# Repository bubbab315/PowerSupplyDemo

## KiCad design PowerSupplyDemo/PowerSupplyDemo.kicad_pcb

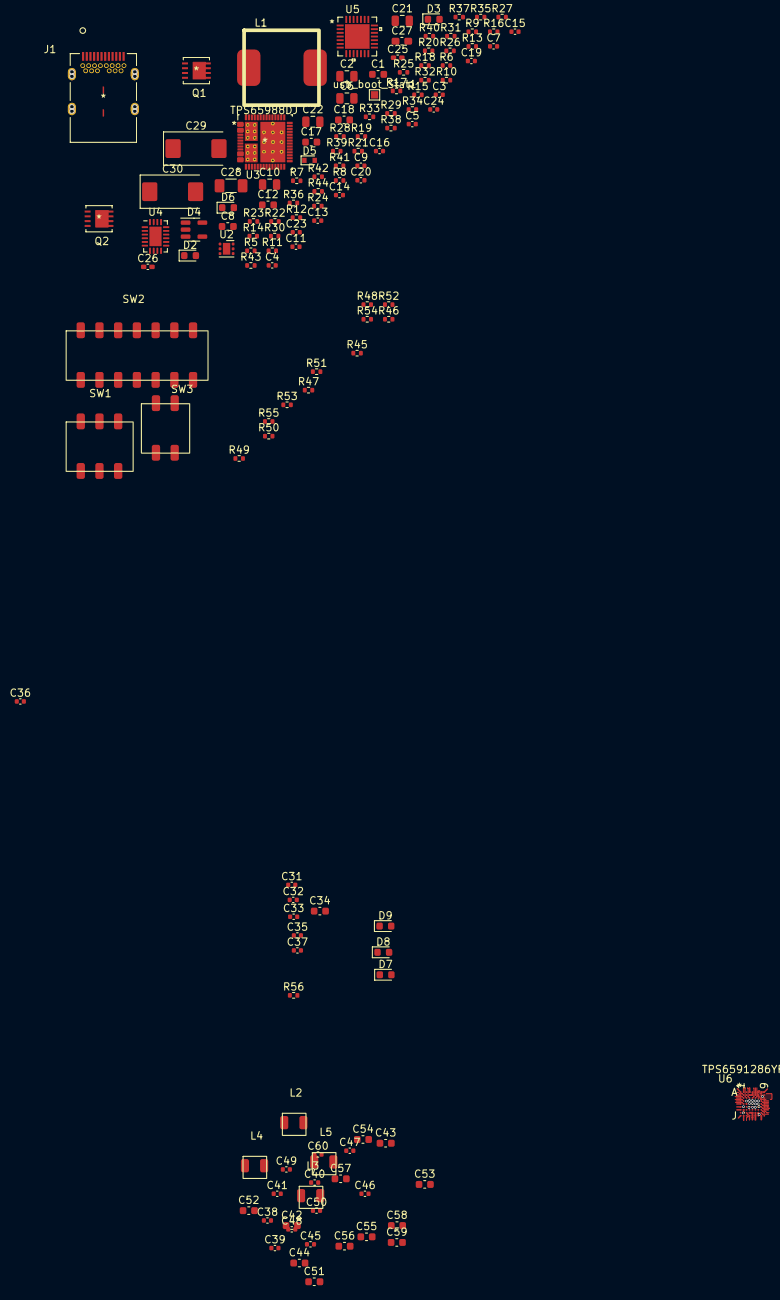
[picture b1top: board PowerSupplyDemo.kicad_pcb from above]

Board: 8 copper layers, 137 parts (0 on the bottom side), 88 nets.

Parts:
C1, C18: 4.7uF; C_0603_1608Metric
C2, C6, C21: 10uF; C_0805_2012Metric
C3: 1000p; C_0402_1005Metric
C4: 200p; C_0402_1005Metric
C5: 470p; C_0402_1005Metric
C7, C16, C24: 1uF; C_0402_1005Metric
C8, C12, C17: 4.7uF 10V; C_0603_1608Metric
C9, C13, C14, C15, C19: 0.1uF; C_0402_1005Metric
C10: 47uF 25V(dnp); C_0805_2012Metric
C11: 0.01uF; C_0402_1005Metric
C20: 77.5n; C_0402_1005Metric
C22: 47uF; C_0805_2012Metric
C23: tbd(opt); C_0402_1005Metric
C25: 2.2uF; C_0402_1005Metric_Pad0.74x0.62mm_HandSolder
C26: 4.7uF; C_0402_1005Metric_Pad0.74x0.62mm_HandSolder
C27: 10uF; C_0603_1608Metric_Pad1.08x0.95mm_HandSolder
C28: 47uF; C_1206_3216Metric_Pad1.33x1.80mm_HandSolder
C29, C30: 100u; CP_EIA-7343-15_Kemet-W
C31, C33, C39, C48, C49, C60: 4.7uF; C_0402_1005Metric
C32, C35, C37: 100nF; C_0402_1005Metric
C34, C42, C43, C44, C51, C52, C53, C54, C55, C56, C57, C58, C59: 10uF; C_0603_1608Metric
C36, C38, C40, C41, C45, C46, C47, C50: 2.2uF; C_0402_1005Metric
D2, D3: D_TVS(dnp); D_0603_1608Metric
D4: SP0504BAHT; SOT-23-5
D5: BAT54XV2T1; D_SOD-523
D6, D9: red; LED_0603_1608Metric
D7: green; LED_0603_1608Metric
D8: yellow; LED_0603_1608Metric
J1: USB_C; USB_C_632723300011
L1: IHLP4040DZER1R0M5A
L2, L3, L4, L5: 1uH; SPM3012T-1R0M
Q1, Q2: BSZ060NE2LSATMA1
R5, R6, R7, R8, R15, R16, R17, R18, R20, R21: 10k; R_0402_1005Metric
R9, R14, R22, R23, R36, R37, R38: 0; R_0402_1005Metric
R10, R24, R27: dnp; R_0402_1005Metric
R11: 101.675k; R_0402_1005Metric
R12: 100k; R_0402_1005Metric
R13: 12k; R_0402_1005Metric
R19: 5; R_0402_1005Metric
R25: 2.2ohm; R_0402_1005Metric
R26: 3k 1%; R_0402_1005Metric
R28, R29, R32, R33: 1k 1%; R_0402_1005Metric
R30: 90.9k; R_0402_1005Metric
R31: 20.0k; R_0402_1005Metric
R34: 150 1%; R_0402_1005Metric
R35: 150; R_0402_1005Metric
R39, R40, R41, R42, R43, R44: 0(DNP); R_0402_1005Metric
R45, R46, R47, R48, R49, R50, R51, R52, R53, R54, R55: 4.7K; R_0402_1005Metric
R56: 0(dnp); R_0402_1005Metric
SW1: 219-3LPSTR
SW2: 219-7LPSTR
SW3: 219-2LPST
U2: TVS2200DRV; WSON-6-1EP_2x2mm_P0.65mm_EP1x1.6mm
U3: TPS65988DJ; TPS65988DHRSHR
U4: LTC3833IUDC; QFN-20-1EP_3x4mm_P0.5mm_EP1.65x2.65mm
U5: CP2102N-A01-GQFN28
U6: TPS6591286YFFR
usb_boot_Stat1: usb_boot_Stat; TestPoint_Pad_1.0x1.0mm

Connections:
/PMIC/EN1: R45.2, SW2.1, U6.E8 (EN1/DCDC1__SEL)
/PMIC/EN2: R47.2, SW2.2, U6.D8 (EN2/DCDC2__SEL)
/PMIC/EN3: R49.2, SW2.3, U6.C6 (EN3/DCDC3__SEL)
/PMIC/EN4: R51.2, SW2.4, U6.C5 (EN4/DCDC4__SEL)
/PMIC/EN_LS0: R54.2, SW2.6, U6.C3 (EN_LS0)
/PMIC/EN_LS1: R53.2, SW2.5, U6.C2 (EN_LS1)
/PMIC/LDOA: C38.1, SW1.4, SW1.5, SW1.6, SW2.8, SW2.9, SW2.10, SW2.11, SW2.12, SW2.13, SW2.14, U6.D3 (NPWRON), U6.G3 (LDOAO)
/PMIC/POS_1P8_IO: C33.1, C35.1, U6.F7 (VDDIO), U6.J1 (VLDO10)
/PMIC/Sleep: R55.2, SW2.7, U6.G4 (SLEEP/PWR__REQ)
/PMIC/config1: R50.2, SW1.3, U6.E2 (CONFIG1)
/PMIC/config2: R48.2, SW1.2, U6.D2 (CONFIG2)
/PMIC/iic_or_spi_cntrl: R46.2, SW1.1, U6.E7 (DEF_SPI__I2C-GPIO)
/input_power/ADCIN1: R33.1, R34.2, U3.6 (ADCIN1)
/input_power/CP2102VDD: C17.1, C19.1, R32.1, U5.6 (VDD)
/input_power/DRAIN1: U3.8 (DRAIN1), U3.15 (DRAIN1), U3.19 (DRAIN1), U3.58 (DRAIN1)
/input_power/DRAIN2: U3.7 (DRAIN2), U3.52 (DRAIN2), U3.56 (DRAIN2), U3.57 (DRAIN2)
/input_power/HRESET: R14.1, U3.44 (HRESET)
/input_power/I2C1_IRQ: R20.1, R38.2, U3.29 (~I2C1_IRQ)
/input_power/I2C1_SCL: R15.1, R36.2, U3.27 (I2C1_SCL)
/input_power/I2C1_SDA: R17.1, R37.2, U3.28 (I2C1_SDA)
/input_power/I2C2_IRQ: R21.1, R41.2, U3.34 (~I2C2_IRQ)
/input_power/I2C2_SCL: R16.1, R39.2, U3.32 (I2C2_SCL)
/input_power/I2C2_SDA: R18.1, R40.2, U3.33 (I2C2_SDA)
/input_power/I2C3_IRQ: R5.1, R44.2, U3.23 (~I2C3_IRQ(GPIO7))
/input_power/I2C3_SCL: R7.1, R42.2, U3.21 (I2C3_SCL(GPIO5))
/input_power/I2C3_SDA: R6.1, R43.2, U3.22 (I2C3_SDA(GPIO6))
/input_power/LDO_1P8: C1.1, U3.35 (LDO_1V8)
/input_power/LDO_3P3: C2.1, R5.2, R6.2, R7.2, R15.2, R16.2, R17.2, R18.2, R20.2, R21.2, R33.2, U3.9 (LDO_3V3)
/input_power/PDVIN_3P3: C6.1, U3.5 (VIN_3V3)
/input_power/Sense+: C20.2, R26.1, R27.2, U4.18 (SENSE+)
/input_power/VCONN1_CC1: D3.2 (A2), J1.A5 (CC), U3.24 (C1_CC1)
/input_power/VCONN1_CC2: D2.2 (A2), J1.B5 (VCONN), U3.26 (C1_CC2)
/input_power/V_RNG: R9.1, R10.2, R12.2, U4.5 (V_RNG)
/input_power/boost: C14.1, R19.1, U4.16 (BOOST)
/input_power/current_sense+: C14.2, L1.1, Q1.1, Q1.2, Q1.3, Q2.5, Q2.6, Q2.7, Q2.8, R26.2, U4.14 (SW)
/input_power/int_vcc: C12.1, D5.2 (A), R9.2, U4.9 (MODE/PLL_IN), U4.11 (INT_VCC)
GND: C1.2, C2.2, C3.2, C4.1, C5.2, C6.2, C7.2, C8.2, C9.2, C10.2, C11.2, C12.2, C13.2, C15.2, C16.2, C17.2, C18.2, C19.2, C21.2, C22.2, C24.2, C25.2, C26.2, C27.2, C28.2, C29.2, C30.2, C31.2, C32.2, C33.2, C34.2, C35.2, C36.2, C37.2, C38.2, C39.2, C40.2, C41.2, C42.2, C43.2, C44.2, C45.2, C46.2, C47.2, C48.2, C49.2, C50.2, C51.2, C52.2, C53.2, C54.2, C55.2, C56.2, C57.2, C58.1, C59.1, C60.2, D2.1 (A1), D3.1 (A1), D4.2 (A), D6.1 (K), J1.25 (SHIELD), J1.26 (SHIELD), J1.27 (SHIELD), J1.28 (SHIELD), J1.29 (SHIELD), J1.30 (SHIELD), J1.A1 (GND), J1.A12 (GND), J1.B1 (GND), J1.B12 (GND), Q2.1, Q2.2, Q2.3, R8.1, R10.1, R11.1, R14.2, R24.2, R29.1, R31.1, R34.1, R45.1, R46.1, R47.1, R48.1, R49.1, R50.1, R51.1, R52.1, R53.1, R54.1, R55.1, U2.1 (GND), U2.2 (GND), U2.3 (GND), U2.7 (GND), U3.20 (GND), U3.36 (SPI_PICO), U3.37 (SPI_PICO), U3.38 (SPI_CLK), U3.39 (~SPI_CS), U3.51 (GND), U3.59 (PPAD), U4.1 (V_OSNS-), U4.12 (SGND), U4.21 (SGND), U5.3 (GND), U6.A5 (PGND4), U6.B4 (VDCDC4_GND), U6.B5 (PGND4), U6.C7 (AGND), U6.E1 (PGND3), U6.E3 (DGND), U6.E9 (PGND2), U6.F3 (AGND), U6.H4 (VDCDC1_GND), U6.H5 (PGND1), U6.J5 (PGND1)
MAIN_5P0: C8.1, C10.1, C15.1, C16.1, C18.1, C21.1, C22.1, R25.2, U3.11 (PP_HV1), U3.12 (PP_HV1)
unnamed: C3.1, U4.3 (TRACK_SS)
unnamed: C4.2, R13.1, U4.4 (ITH)
unnamed: C5.1, R13.2
unnamed: C13.1, Q1.5, Q1.6, Q1.7, Q1.8, R25.1, U4.10 (V_IN)
unnamed: C23.1, R30.1, R31.2, U4.2 (V_OSNS+)
unnamed: C37.1, U6.H3 (VREF1V25)
unnamed: C39.1, U6.F1 (VINLDO4)
unnamed: C40.1, U6.A2 (VINLDO67)
unnamed: C41.1, U6.J8 (VINLDO9)
unnamed: C45.1, U6.J2 (VINLDO1210)
unnamed: C46.1, U6.F8 (VINLDO3)
unnamed: C47.1, U6.F9 (VLDO3)
unnamed: C48.1, U6.G8 (VINLDO5)
unnamed: C49.1, U6.G9 (VLDO5)
unnamed: C50.1, U6.H8 (VINLDO8)
unnamed: D5.1 (K), R19.2
unnamed: D6.2 (A), R35.1
unnamed: D7.1 (K), U6.B2 (LEDB/GPIO4)
unnamed: D9.1 (K), U6.B1 (LEDC/GPIO5)
unnamed: L2.1, U6.H6 (SW1), U6.J6 (SW1)
unnamed: L3.1, U6.D9 (SW2)
unnamed: L4.1, U6.D1 (SW3)
unnamed: L5.1, U6.A6 (SW4), U6.B6 (SW4)
unnamed: Q1.4 (G), R23.2, R24.1
unnamed: Q2.4 (G), R22.2
unnamed: R8.2, U3.17 (GPIO1)
unnamed: R11.2, U4.6 (RT)
unnamed: R12.1, U4.17 (C_PGOOD)
unnamed: R22.1, U4.13 (BG)
unnamed: R23.1, U4.15 (TG)
unnamed: R28.1, R29.2, U5.8 (VBUS)
unnamed: R32.2, U5.9 (RSTB)
unnamed: R56.1, U6.C4 (GPIO2__CE)
unnamed: U3.16 (GPIO0), usb_boot_Stat1.1
PMIC_ENABLE: R52.2, SW3.4, U6.D6 (PWRHOLD_ON)
POS0P85: C43.1, L2.2, U6.J4 (VDCDC1)
POS1P2_VMEM: C44.1, C56.1, C57.1, L5.2, U6.A4 (VDCDC4)
POS1P8_C0: C51.1, L3.2, U6.D7 (VDCDC2)
POS3P3_C0: C52.1, L4.2, U6.F2 (VDCDC3)
POS3P3_MCU: C60.1, U6.G1 (VLDO4)
USB0_DM: D4.5 (K), J1.A7 (Dn1), U5.5 (D-)
USB0_DP: D4.4 (K), J1.A6 (Dp1), U5.4 (D+)
USB1_DM: D4.3 (K), J1.B7 (Dn2)
USB1_DP: D4.1 (K), J1.B6 (Dp2)
USB_I2C_IRQ: R38.1, R41.1, R44.1
USB_I2C_SCL: R36.1, R39.1, R42.1
USB_I2C_SDA: R37.1, R40.1, R43.1
USB_PWR_VBUS: C7.1, C9.1, C11.1, J1.A4 (VBUS), J1.A9 (VBUS), J1.B4 (VBUS), J1.B9 (VBUS), R28.2, R35.2, U2.4 (IN), U2.5 (IN), U2.6 (IN), U3.13 (VBUS1), U3.14 (VBUS1), U5.7 (VREGIN)
VSYS_3P3: C20.1, C23.2, C24.1, C25.1, C26.1, C27.1, C28.1, C29.1, C30.1, C31.1, C32.1, C34.1, C36.1, C42.1, C53.1, C54.1, C55.1, C58.2, C59.2, D7.2 (A), D8.2 (A), D9.2 (A), L1.2, R27.1, R30.2, SW3.1, U4.19 (SENSE-), U4.20 (VOUT), U6.A7 (VINDCDC4), U6.B7 (VINDCDC4), U6.B8 (LSI), U6.B9 (LSI), U6.C1 (VINDCDC3), U6.C8 (VINDCDC__ANA), U6.C9 (VINDCDC2), U6.G2 (VCCS/VIN__MON), U6.H2 (VCC), U6.H7 (VINDCDC1), U6.J7 (VINDCDC1)
VSYS_3P3_SDIO: U6.A8 (LSO), U6.A9 (LSO)

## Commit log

2023-03-31 initial commit, copied over current power circuitry from SitariDev
2023-03-31 organized the pmic stuff in pcb land
2024-04-08 began laying out the tps
2024-04-11 thickened outside fanout, and replaced inner levels with vip
2024-04-11 updated filled area parameters as well as trace widths for 0.4mm bga on pmic
2024-04-11 updated constraints again.
2024-04-19 created a demo file to show alex how to add commit messages

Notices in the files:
parts and their libraries:
Copyright 2021 Accelerated Designs. All rights reserved.
Copyright 2016 Accelerated Designs. All rights reserved.
